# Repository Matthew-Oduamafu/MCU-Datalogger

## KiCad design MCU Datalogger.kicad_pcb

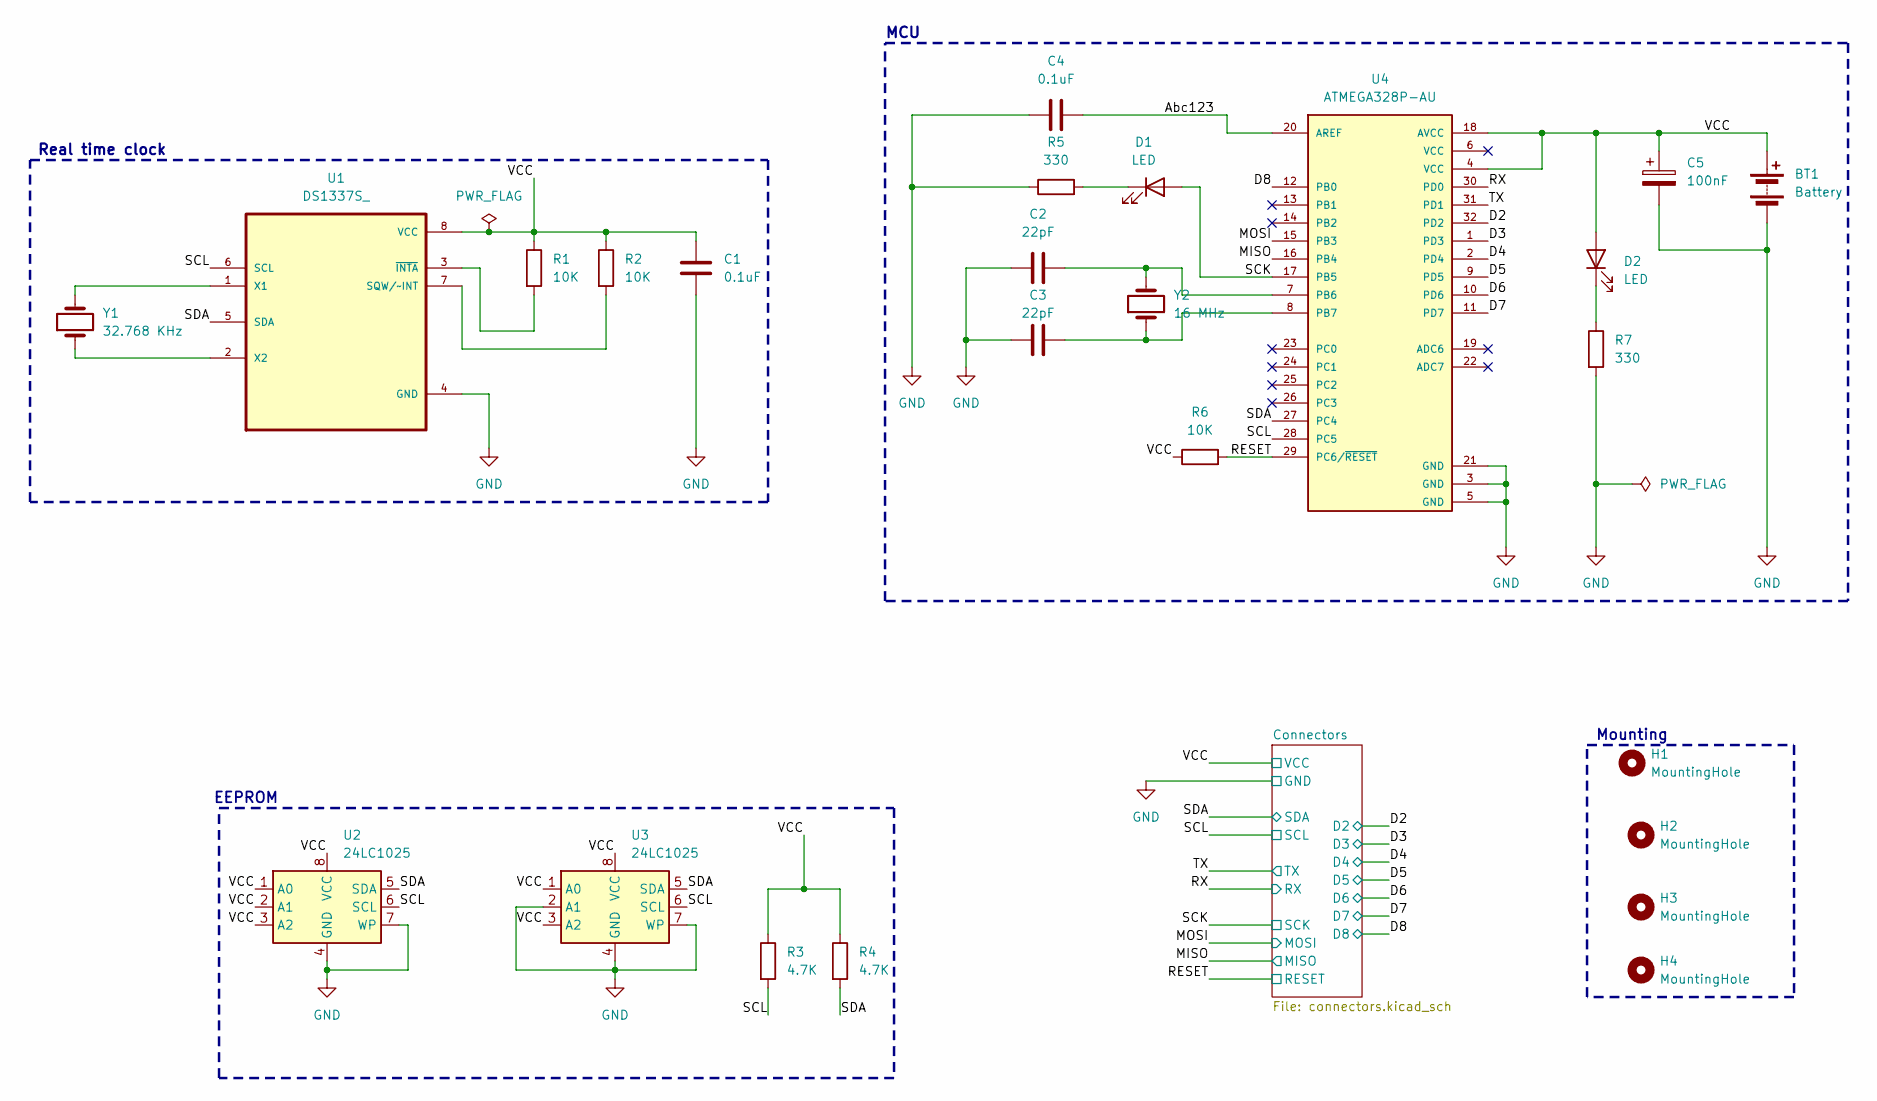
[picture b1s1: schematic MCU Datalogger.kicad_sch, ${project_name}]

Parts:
BT1: Battery; PinHeader_2x01_P2.54mm_Vertical
C1, C4: 0.1uF; C_0805_2012Metric
C2, C3: 22pF; C_0805_2012Metric
C5: 100nF; C_0805_2012Metric
D1, D2: LED; LED_0805_2012Metric
H1, H2, H3, H4: MountingHole; MountingHole_2.1mm
R1, R2, R6: 10K; R_0805_2012Metric
R3, R4: 4.7K; R_0805_2012Metric
R5, R7: 330; R_0805_2012Metric
U1: DS1337S_; SOIC127P600X175-8N
U2, U3: 24LC1025; SOIC-8_5.3x5.3mm_P1.27mm
U4: ATMEGA328P-AU; QFP80P900X900X120-32N; PARTREV 8271A
Y1: 32.768 KHz; Crystal_SMD_5032-2Pin_5.0x3.2mm_HandSoldering
Y2: 16 MHz; Crystal_SMD_5032-2Pin_5.0x3.2mm_HandSoldering

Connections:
/Abc123: C4.2, U4.20 (AREF)
/D2: U4.32 (PD2); also elsewhere on the board
/D3: U4.1 (PD3); also elsewhere on the board
/D4: U4.2 (PD4); also elsewhere on the board
/D5: U4.9 (PD5); also elsewhere on the board
/D6: U4.10 (PD6); also elsewhere on the board
/D7: U4.11 (PD7); also elsewhere on the board
/D8: U4.12 (PB0); also elsewhere on the board
/MISO: U4.16 (PB4); also elsewhere on the board
/MOSI: U4.15 (PB3); also elsewhere on the board
/RESET: R6.2, U4.29 (PC6/~RESET); also elsewhere on the board
/RX: U4.30 (PD0); also elsewhere on the board
/SCK: D1.2 (A), U4.17 (PB5); also elsewhere on the board
/SCL: R3.2, U1.6 (SCL), U2.6 (SCL), U3.6 (SCL), U4.28 (PC5); also elsewhere on the board
/SDA: R4.2, U1.5 (SDA), U2.5 (SDA), U3.5 (SDA), U4.27 (PC4); also elsewhere on the board
/TX: U4.31 (PD1); also elsewhere on the board
/VCC: BT1.1 (+), C1.1, C5.1, D2.2 (A), R1.1, R2.1, R3.1, R4.1, R6.1, U1.8 (VCC), U2.1 (A0), U2.2 (A1), U2.3 (A2), U2.8 (VCC), U3.1 (A0), U3.3 (A2), U3.8 (VCC), U4.4 (VCC), U4.18 (AVCC); also elsewhere on the board
GND: BT1.2 (-), C1.2, C2.1, C3.1, C4.1, C5.2, R5.1, R7.2, U1.4 (GND), U2.4 (GND), U2.7 (WP), U3.2 (A1), U3.4 (GND), U3.7 (WP), U4.3 (GND), U4.5 (GND), U4.21 (GND); also elsewhere on the board
unnamed: D1.1 (K), R5.2
unnamed: D2.1 (K), R7.1
unnamed: R2.2, U1.7 (SQW/~INT)
unnamed: U1.1 (X1), Y1.2
unnamed: U1.2 (X2), Y1.1
unnamed: R1.2, U1.3 (~INTA)
unnamed: C2.2, U4.7 (PB6), Y2.2
unnamed: C3.2, U4.8 (PB7), Y2.1

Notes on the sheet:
EEPROM
MCU
Real time clock
Mounting

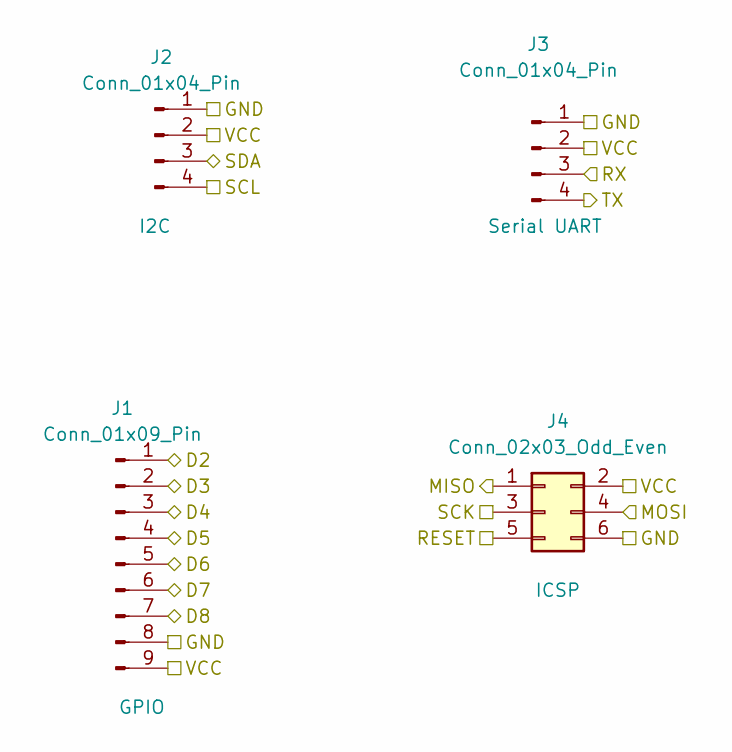
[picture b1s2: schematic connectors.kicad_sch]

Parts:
J1: Conn_01x09_Pin; PinHeader_1x09_P2.54mm_Vertical
J2, J3: Conn_01x04_Pin; PinHeader_1x04_P2.54mm_Vertical
J4: Conn_02x03_Odd_Even; PinHeader_2x03_P2.54mm_Vertical

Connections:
/D2: J1.1; also elsewhere on the board
/D3: J1.2; also elsewhere on the board
/D4: J1.3; also elsewhere on the board
/D5: J1.4; also elsewhere on the board
/D6: J1.5; also elsewhere on the board
/D7: J1.6; also elsewhere on the board
/D8: J1.7; also elsewhere on the board
/MISO: J4.1; also elsewhere on the board
/MOSI: J4.4; also elsewhere on the board
/RESET: J4.5; also elsewhere on the board
/RX: J3.3; also elsewhere on the board
/SCK: J4.3; also elsewhere on the board
/SCL: J2.4; also elsewhere on the board
/SDA: J2.3; also elsewhere on the board
/TX: J3.4; also elsewhere on the board
/VCC: J1.9, J2.2, J3.2, J4.2; also elsewhere on the board
GND: J1.8, J2.1, J3.1, J4.6; also elsewhere on the board

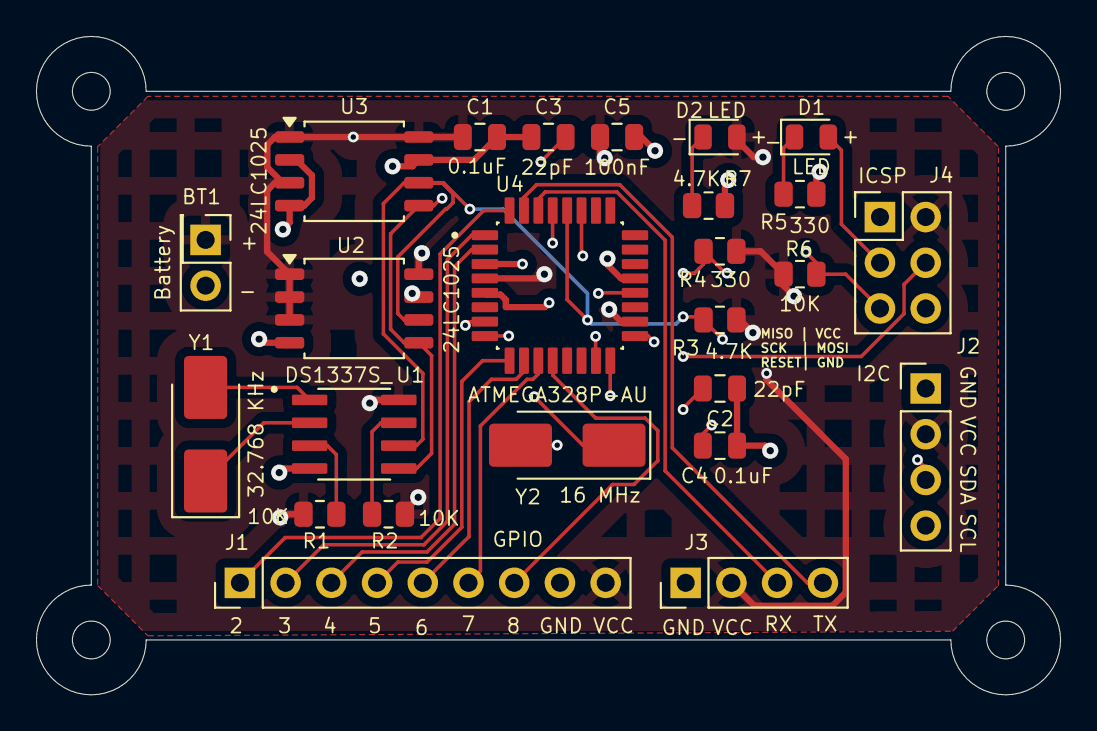
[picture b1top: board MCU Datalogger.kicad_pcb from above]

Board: 4 copper layers, 56.9 x 36.6 mm, 29 parts (0 on the bottom side), 26 nets.

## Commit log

2025-12-21 schema page settings
2025-12-21 Add schem symbols'
2025-12-21 finish schema design
2025-12-21 layout component placement
2025-12-21 update conn_02x03 footprint
2025-12-23 arrange component on layout
2025-12-24 finish routing
2025-12-24 finish 2 layer route
2025-12-24 finish 2 layer
2025-12-24 finish 4 layer pcb
2025-12-24 add gitattributes file
2025-12-24 add net label to schematic
2025-12-24 fix wrong SCL/SCK connection
2025-12-25 update SCL route on pcb
2025-12-25 update SCL connection
2025-12-25 add custom logo
